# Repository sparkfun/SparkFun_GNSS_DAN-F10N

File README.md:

SparkFun Dualband L1/L5 GNSS Breakout - DAN-F10N
========================================

[*SparkFun Dualband L1/L5 GNSS Breakout - DAN-F10N (GPS-28435)*](https://www.sparkfun.com/sparkfun-dualband-l1-l5-gnss-breakout-dan-f10n.html)

The SparkFun DAN-F10N Dualband GNSS Breakout is built around the powerful u-blox F10 engine, offering simultaneous reception of L1 and L5 frequency bands. This board leverages u-blox's advanced multipath mitigation technology to isolate the strongest signals, delivering reliable, meter-level position accuracy even in dense urban canyons. To ensure signal integrity, the module incorporates a robust SAW-LNA-SAW RF front-end with an additional notch filter (LTE B13), providing excellent rejection of interference from nearby cellular modems.

The SparkFun Dualband L1/L5 GNSS Breakout - DAN-F10N features u-blox's dual-band GNSS technology for the L1/L5 frequency bands. Their proprietary dual-band multipath mitigation technology enables the u-blox F10 GNSS engine to isolate the best signals from the L1 and L5 bands; delivering a solid meter-level position accuracy in challenging urban environments. Additionally, the DAN-F10N module's robust SAW-LNA-SAW RF architecture with an additional notch filter (LTE B13) on the L1 RF path ensures the best possible out-of-band interference mitigation from nearby cellular modems.

The DAN-F10N GNSS module on this board comes with a 20 x 20 x 8 mm, integrated, Right Hand Circular Polarized (RHCP), L1/L5 dual-band patch antenna that offers the best compromise between size and performance. The patch antenna's wide beamwidth provides flexibility in the device's orientation; while alternatively, the module also has an antenna switch function to give users the option to utilize an external dual-band antenna, further increasing its utility.

The DAN-F10N module is supported by the u-blox u-center 2 GNSS software for real-time performance analysis, receiver configuration, and data logging. The AssistNow Online, Offline, and Autonomous A-GNSS services can also be used with the module for faster satellite acquisition. Users can also interface with the GNSS module using NMEA 4.11 and UBX binary protocols.

> [!NOTE]
> The GPS `L5` signals are currently, considered as *"pre-operational"* and not utilized by default in navigation solutions. However, it is possible override the receiver's configuration to evaluate the GPS `L5` signals. Please refer to the integration manual for more details.
> 
> This is an operational limitation of the satellite/space segment and not an issue of the u-blox product.

Documentation
-------------

- **[Hookup Guide (mkdocs)](http://docs.sparkfun.com/SparkFun_GNSS_DAN-F10N/)** - A hookup guide for the SparkFun DAN-F10N Dualband L1/L5 GNSS breakout board hosted by GitHub pages.<br>
   
- [SparkFun u-blox GNSS v3 Arduino Library](https://github.com/sparkfun/SparkFun_u-blox_GNSS_v3) - An Arduino library for the u-blox GNSS module

Repository Contents
-------------------

- **[/docs](/docs/)** - Online documentation files
  - [/assets](/docs/assets/) - Assets files
    - [/3d_model](/docs/assets/3d_model/) - 3D models for the board
    - [/board_files](/docs/assets/board_files/) - Design files for the board
      - [KiCad Design Files](/docs/assets/board_files/kicad_files.zip) (.zip)
      - [Schematic](/docs/assets/board_files/schematic.pdf) (.pdf)
      - [Dimensions](/docs/assets/board_files/dimensions.pdf) (.pdf)
    - [/component_documentation](/docs/assets/component_documentation/) - Datasheets for hardware components
    - [/img/hookup_guide](/docs/assets/img/hookup_guide/) - Images for hookup guide documentation - Hookup guide images for the board
    - /Hardware - Hardware design files (.brd, .sch)
      - /Production - Production files

Product Variants
----------------

- [GPS-28435](https://www.sparkfun.com/sparkfun-dualband-l1-l5-gnss-breakout-dan-f10n.html) - Breakout Board
- [GPS-29061](https://www.sparkfun.com/sparkpnt-gnss-flex-module-dan-f10n.html) - SparkPNT GNSS Flex Module
- [GPS-29491](https://www.sparkfun.com/sparkfun-gnss-flex-phat-dan-f10n.html) - SparkFun GNSS Flex pHAT *(kit)*

Version History
---------------

- [v10](https://github.com/sparkfun/SparkFun_GNSS_DAN-F10N/releases/tag/v10) - Initial Release

License Information
-------------------

This product is ***open source***!

Please review the [`LICENSE.md`](./LICENSE.md) file for license information.

If you have any questions or concerns about licensing, please contact technical support on our [SparkFun forums](https://forum.sparkfun.com/viewforum.php?f=152).

Distributed as-is; no warranty is given.

- Your friends at SparkFun.

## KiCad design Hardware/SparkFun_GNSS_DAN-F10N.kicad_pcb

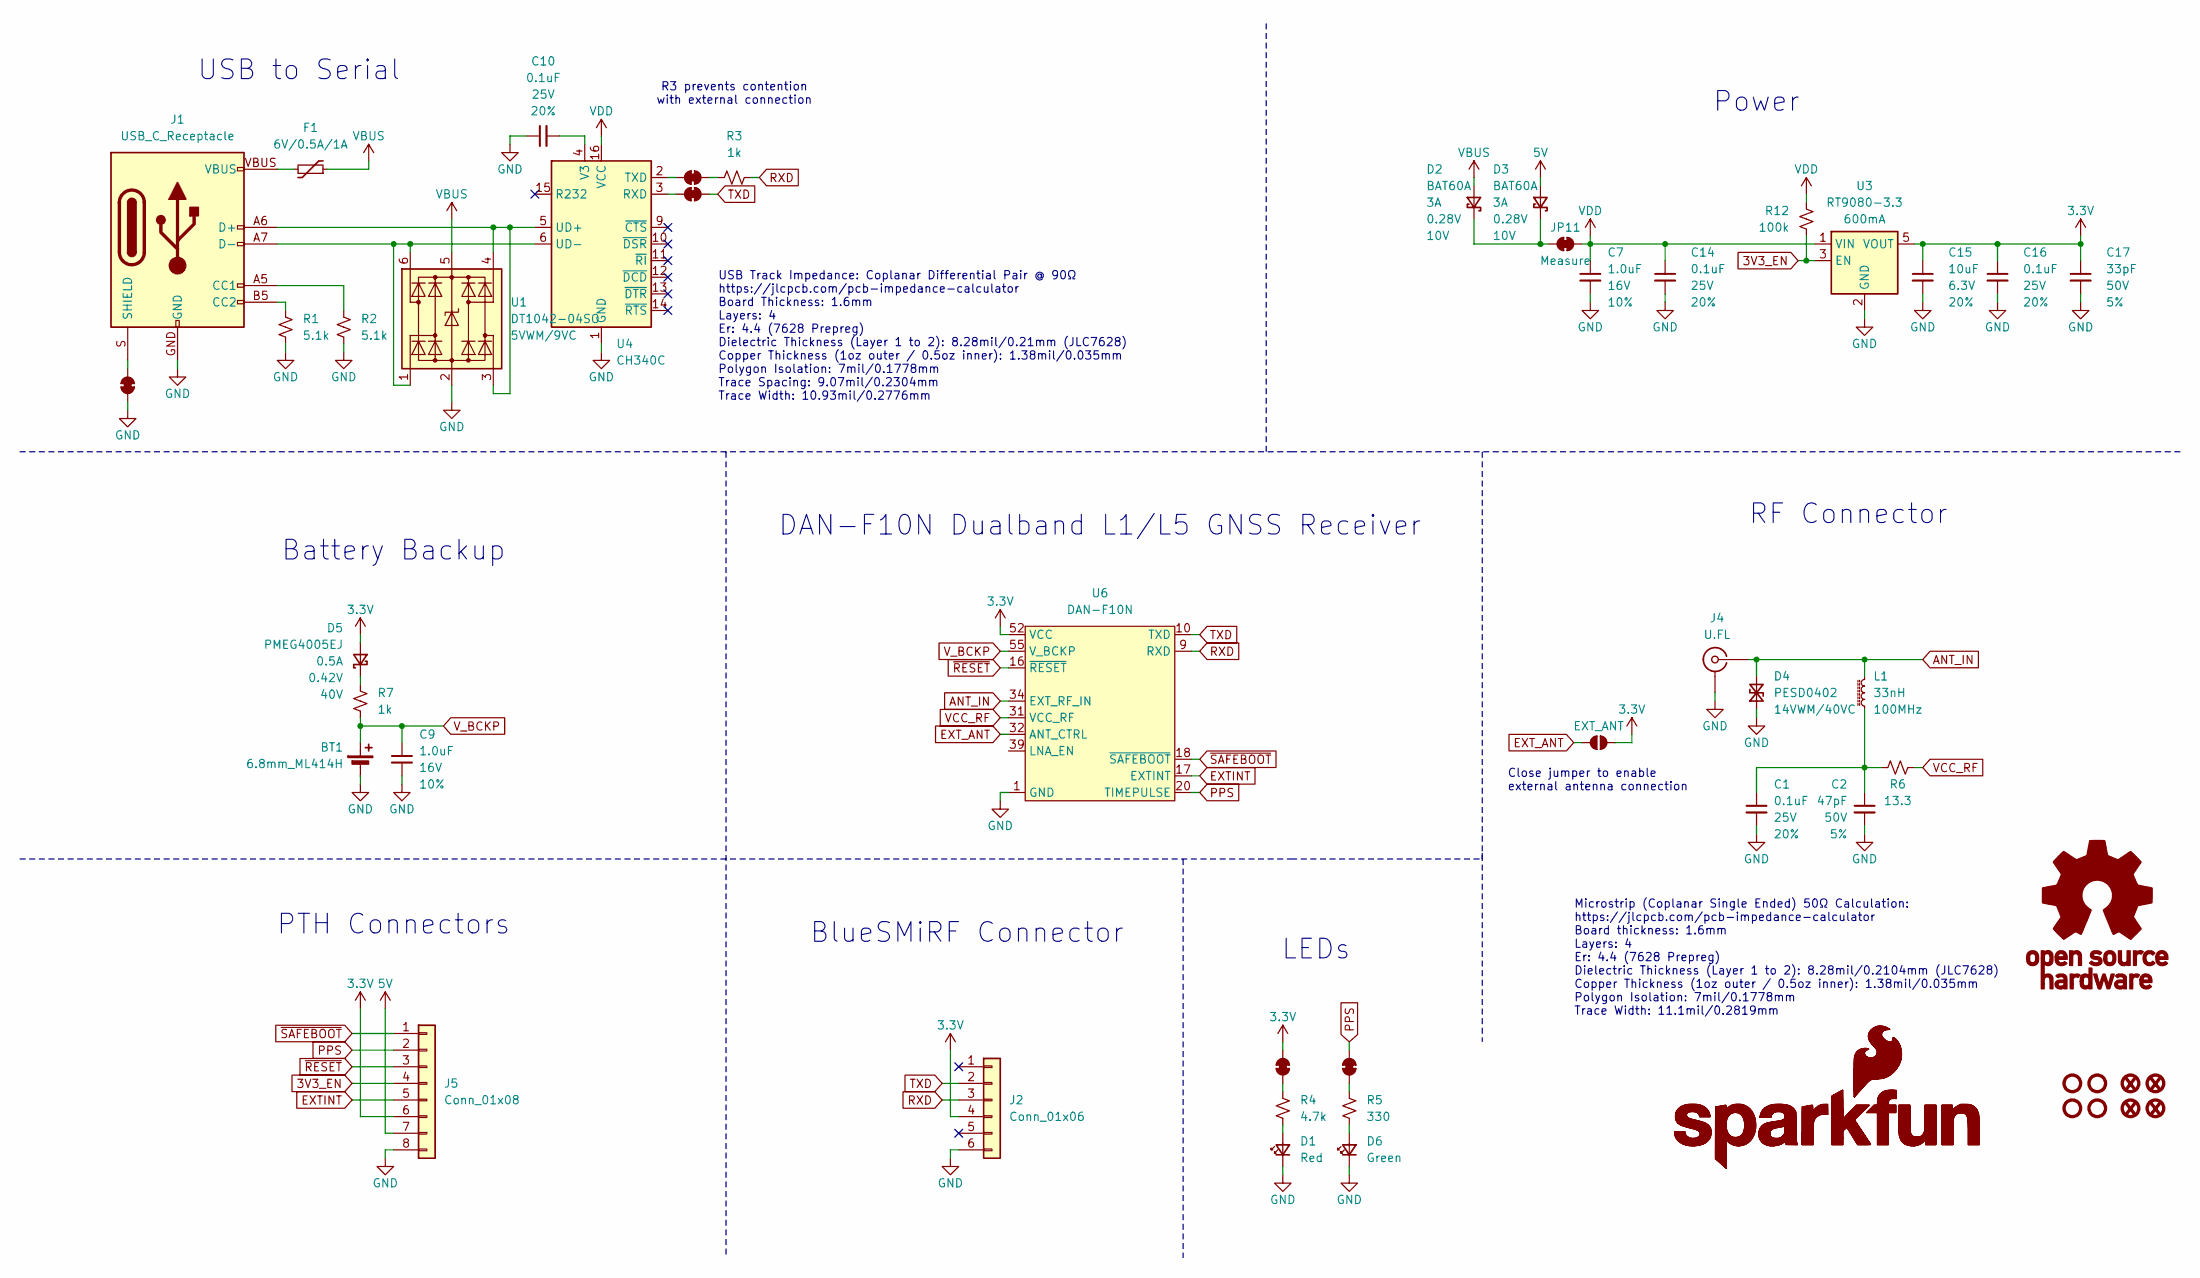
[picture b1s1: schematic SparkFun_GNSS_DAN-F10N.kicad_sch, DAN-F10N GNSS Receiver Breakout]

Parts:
BT1: 6.8mm_ML414H; ML414H_IV01E
C1, C10, C14, C16: 0.1uF; C_0603_1608Metric; Voltage 25V; Tolerance 20%
C2: 47pF; C_0603_1608Metric; Voltage 50V; Tolerance 5%
C7, C9: 1.0uF; C_0603_1608Metric; Voltage 16V; Tolerance 10%
C15: 10uF; C_0603_1608Metric; Voltage 6.3V; Tolerance 20%
C17: 33pF; C_0603_1608Metric; Voltage 50V; Tolerance 5%
D1: Red; LED_0603_1608Metric_Red
D2, D3: BAT60A; SOD-323
D4: PESD0402; C_0402_1005Metric; Rating 14VWM/40VC
D5: PMEG4005EJ; SOD-323
D6: Green; LED_1206_Bottom_Green
F1: 6V/0.5A/1A; 0805
FID1, FID2, FID3, FID4: Fiducial_0.5mm; Fiducial_0.5mm_Mask1mm
G1: OSHW_Logo; Creative_Commons_License
G3: SparkFun_Logo
G5: SparkFun_Logo; SparkFun_Logo_8mm
J1: USB_C_Receptacle; USB-C_16
J2: Conn_01x06; 1x06
J4: U.FL
J5: Conn_01x08; 1x08
JP1: EXT_ANT; Jumper_2_NO
JP2, JP3, JP7, JP9, JP10: Jumper_2_NC_Trace
JP11: Measure; Jumper_2_PTH_SMD_Combo-NC
L1: 33nH; C_0603_1608Metric
R1, R2: 5.1k; R_0603_1608Metric
R3, R7: 1k; R_0603_1608Metric
R4: 4.7k; R_0603_1608Metric
R5: 330; R_0603_1608Metric
R6: 13.3; R_2512_6332Metric
R12: 100k; R_0603_1608Metric
ST1, ST2, ST3, ST4: Standoff
U1: DT1042-04SO; SOT23-6; Rating 5VWM/9VC
U3: RT9080-3.3; SOT23-5
U4: CH340C; SO-16
U6: DAN-F10N

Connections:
3.3V: C15.1, C16.1, C17.1, D5.2 (A), J2.4, J5.6, JP1.1 (A), JP2.2 (B), U3.5 (VOUT), U6.52 (VCC), U6.53 (VCC)
3V3_EN: J5.4, R12.1, U3.3 (EN)
5V: D3.2 (A), J5.7
ANT_IN: D4.2 (A2), J4.1 (In), L1.2, U6.34 (EXT_RF_IN)
EXTINT: J5.5, U6.17 (EXTINT)
EXT_ANT: JP1.2 (B), U6.32 (ANT_CTRL)
GND: BT1.-, C1.2, C2.2, C7.2, C9.2, C10.1, C14.2, C15.2, C16.2, C17.2, D1.1 (K), D4.1 (A1), D6.1 (K), J1.GND, J2.6, J4.2 (Ext), J5.8, JP7.1 (A), R1.1, R2.1, U1.2 (GND), U3.2 (GND), U4.1 (GND), U6.1 (GND), U6.2 (GND), U6.3 (GND), U6.4 (GND), U6.5 (GND), U6.6 (GND), U6.7 (GND), U6.8 (GND), U6.13 (GND), U6.14 (GND), U6.15 (GND), U6.19 (GND), U6.21 (GND), U6.22 (GND), U6.23 (GND), U6.26 (GND), U6.27 (GND), U6.28 (GND), U6.29 (GND), U6.30 (GND), U6.33 (GND), U6.35 (GND), U6.37 (GND), U6.38 (GND), U6.40 (GND), U6.41 (GND), U6.42 (GND), U6.43 (GND), U6.44 (GND), U6.47 (GND), U6.48 (GND), U6.49 (GND), U6.50 (GND), U6.51 (GND), U6.54 (GND), U6.56 (GND), U6.57 (GND)
unnamed: C1.1, C2.1, L1.1, R6.2
unnamed: D1.2 (A), R4.1
unnamed: D2.1 (K), D3.1 (K), JP11.1 (A)
unnamed: D5.1 (K), R7.2
unnamed: D6.2 (A), R5.1
unnamed: F1.2, J1.VBUS
unnamed: J1.A5 (CC1), R2.2
unnamed: J1.B5 (CC2), R1.2
unnamed: J1.S (SHIELD), JP7.2 (B)
unnamed: JP2.1 (A), R4.2
unnamed: JP3.1 (A), R5.2
unnamed: JP9.1 (A), U4.2 (TXD)
unnamed: JP9.2 (B), R3.2
unnamed: JP10.1 (A), U4.3 (RXD)
unnamed: J1.A7 (D-), J1.B7 (D-), U1.1 (I/O1), U1.6 (I/O4), U4.6 (UD-)
unnamed: J1.A6 (D+), J1.B6 (D+), U1.3 (I/O2), U1.4 (I/O3), U4.5 (UD+)
unnamed: C10.2, U4.4 (V3)
PPS: J5.2, JP3.2 (B), U6.20 (TIMEPULSE)
RXD: J2.3, R3.1, U6.9 (RXD)
TXD: J2.2, JP10.2 (B), U6.10 (TXD)
VBUS: D2.2 (A), F1.1, U1.5 (VCC)
VCC_RF: R6.1, U6.31 (VCC_RF)
VDD: C7.1, C14.1, JP11.2 (B), R12.2, U3.1 (VIN), U4.16 (VCC)
V_BCKP: BT1.+, C9.1, R7.1, U6.55 (V_BCKP)
~RESET: J5.3, U6.16 (~RESET)
~SAFEBOOT: J5.1, U6.18 (~SAFEBOOT)

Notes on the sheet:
Close jumper to enable external antenna connection
R3 prevents contention with external connection
Microstrip (Coplanar Single Ended) 50Ω Calculation: https://jlcpcb.com/pcb-impedance-calculator Board thickness: 1.6mm Layers: 4 Er: 4.4 (7628 Prepreg) Dielectric Thickness (Layer 1 to 2): 8.28mil/0.2104mm (JLC7628) Copper Thickness (1oz outer / 0.5oz inner): 1.38mil/0.035mm Polygon Isolation: 7mil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
USB Track Impedance: Coplanar Differential Pair @ 90Ω https://jlcpcb.com/pcb-impedance-calculator Board Thickness: 1.6mm Layers: 4 Er: 4.4 (7628 Prepreg) Dielectric Thickness (Layer 1 to 2): 8.28mil/0.21mm (JLC7628) Copper Thickness (1oz outer / 0.5oz inner): 1.38mil/0.035mm Polygon Isolation: 7mil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
RF Connector
BlueSMiRF Connector
LEDs
DAN-F10N Dualband L1/L5 GNSS Receiver
USB to Serial
Battery Backup
Power
PTH Connectors

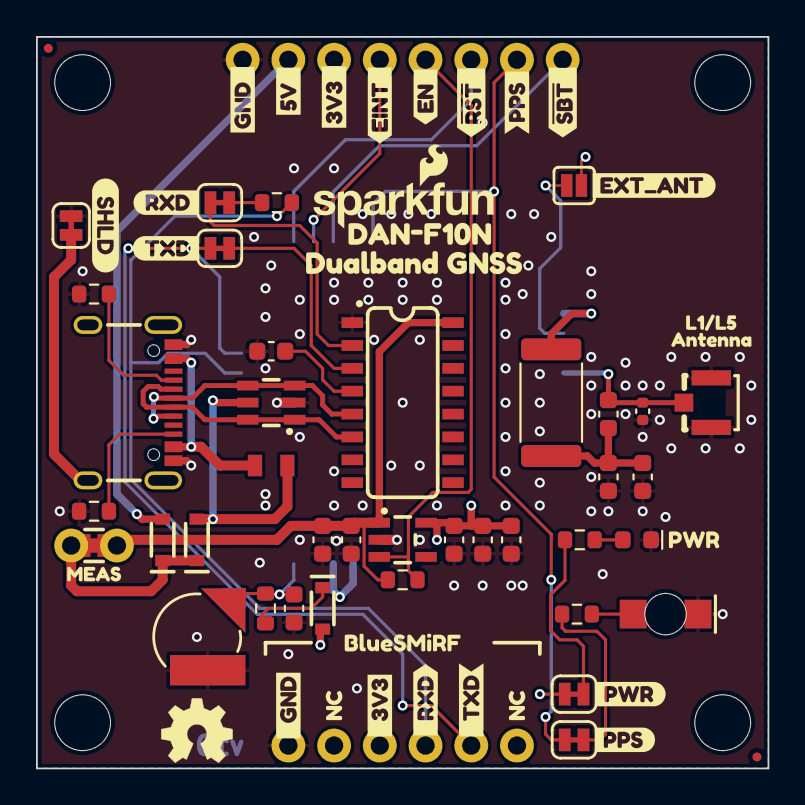
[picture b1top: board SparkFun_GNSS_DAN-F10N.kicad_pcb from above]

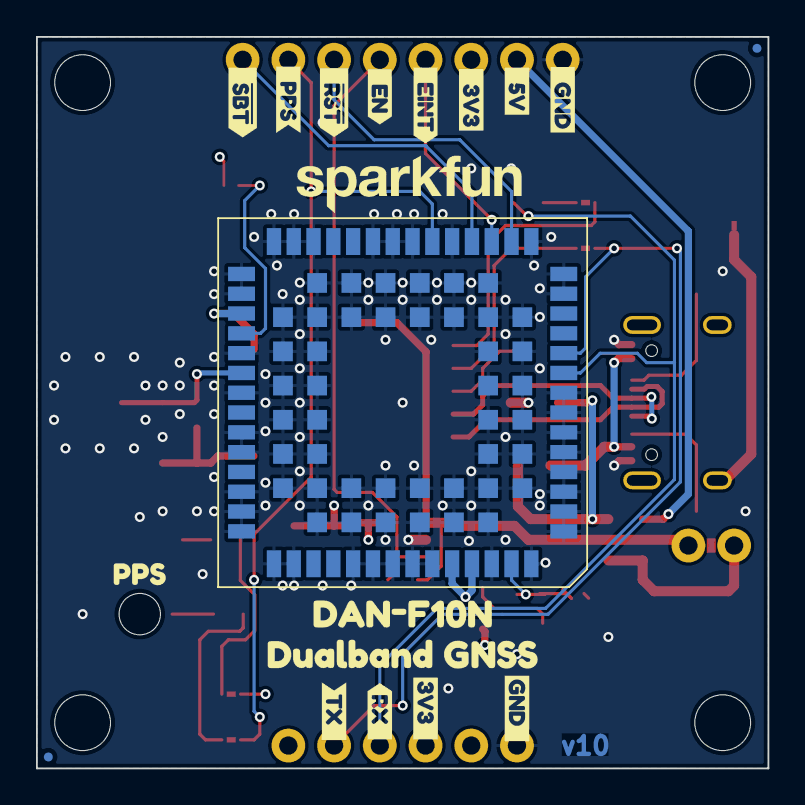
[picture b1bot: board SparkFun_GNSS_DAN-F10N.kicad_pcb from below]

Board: 4 copper layers, 40.6 x 40.6 mm, 93 parts (18 on the bottom side), 33 nets.

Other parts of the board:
Ref**: Val**; OSHW_Logo_4mm
kibuzzard-64C2E6A3: G***; kibuzzard-64C2E6A3
kibuzzard-64C3DF93: G***; kibuzzard-64C3DF93
kibuzzard-67C7D06A: G***; kibuzzard-67C7D06A
kibuzzard-67C7D061: G***; kibuzzard-67C7D061
kibuzzard-67C52A06: G***; kibuzzard-67C52A06
kibuzzard-67C52AED: G***; kibuzzard-67C52AED
kibuzzard-67C52B01: G***; kibuzzard-67C52B01
kibuzzard-67C52B1C: G***; kibuzzard-67C52B1C
kibuzzard-67C52C8F: G***; kibuzzard-67C52C8F
kibuzzard-67C52CCE: G***; kibuzzard-67C52CCE
kibuzzard-67C52D79: G***; kibuzzard-67C52D79
kibuzzard-67C52D85: G***; kibuzzard-67C52D85
kibuzzard-67C52DD7: G***; kibuzzard-67C52DD7
kibuzzard-67C52DE1: G***; kibuzzard-67C52DE1
kibuzzard-67C52F63: G***; kibuzzard-67C52F63
kibuzzard-67C524B9: G***; kibuzzard-67C524B9
kibuzzard-67C524C4: G***; kibuzzard-67C524C4
kibuzzard-67C526AF: G***; kibuzzard-67C526AF
kibuzzard-67C526C1: G***; kibuzzard-67C526C1
kibuzzard-67C526DE: G***; kibuzzard-67C526DE
kibuzzard-67C526ED: G***; kibuzzard-67C526ED
kibuzzard-67C526F3: G***; kibuzzard-67C526F3
kibuzzard-67C526FD: G***; kibuzzard-67C526FD
kibuzzard-67C527CA: G***; kibuzzard-67C527CA
kibuzzard-67C529FB: G***; kibuzzard-67C529FB
kibuzzard-67C5273C: G***; kibuzzard-67C5273C
kibuzzard-67C5274E: G***; kibuzzard-67C5274E
kibuzzard-67C5275D: G***; kibuzzard-67C5275D
kibuzzard-67C5279A: G***; kibuzzard-67C5279A
kibuzzard-67C52692: G***; kibuzzard-67C52692
kibuzzard-67C52701: G***; kibuzzard-67C52701
kibuzzard-67C52734: G***; kibuzzard-67C52734
kibuzzard-67C52738: G***; kibuzzard-67C52738
kibuzzard-67C52789: G***; kibuzzard-67C52789
kibuzzard-67D33FB6, kibuzzard-67D33FB6#2: G***; kibuzzard-67D33FB6
kibuzzard-67D358AB: G***; kibuzzard-67D358AB
kibuzzard-67D3586F: G***; kibuzzard-67D3586F
kibuzzard-67D3589A: G***; kibuzzard-67D3589A
kibuzzard-67D35894: G***; kibuzzard-67D35894
kibuzzard-67EB0CBA: G***; kibuzzard-67EB0CBA
kibuzzard-6501FDDA: G***; kibuzzard-6501FDDA

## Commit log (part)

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2025-03-13 Add ignore
2025-03-31 Fix DAN-F10N footprint. Move EXT_ANT to jumper.
2025-04-03 Fix standoff location. Update to v9.
2025-04-15 Reduce paste on signal pads. Correct EXT_ANT activation level.
2025-04-15 Add panel
2025-04-16 Update PCB details
2025-09-04 Deployed ced2c98 with MkDocs version: 1.6.1
2025-09-04 Deployed 6a5475f with MkDocs version: 1.6.1
2025-09-04 Initial Docs Commit
2025-09-04 Deployed 54ff8e1 with MkDocs version: 1.6.1
2025-09-10 Update .gitignore
    Remove leftover merge conflict markers
    Consolidate duplicate entries
2025-09-10 Deployed 2b0ab12 with MkDocs version: 1.6.1
2025-09-12 Remove local FP/SYM. Update to main kicad library.
2025-09-12 Deployed c091273 with MkDocs version: 1.6.1
2025-09-17 Update KiCAD files
    Updates footprint position for 3D model
2025-09-17 Deployed 373f432 with MkDocs version: 1.6.1
2025-10-10 Update docs
    Adds favicon
    Update link
    Fix styling
2025-10-10 Update workflow
    Use requirements.txt to install dependencies
    Remove git-authors plugin
2025-10-10 Deployed 50b66fa with MkDocs version: 1.6.1
2026-06-03 Deployed ab62904 with MkDocs version: 1.6.1

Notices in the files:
parts and their libraries:
https://creativecommons.org/licenses/by-sa/4.0
Released under the Creative Commons Attribution Share-Alike 4.0 License
